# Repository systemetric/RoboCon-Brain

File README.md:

# RoboCon-Brain
Custom hardware and firmware for the RoboCon Brain, with PCB designs, embedded software and supporting files. Generations are documented through dedicated branches.

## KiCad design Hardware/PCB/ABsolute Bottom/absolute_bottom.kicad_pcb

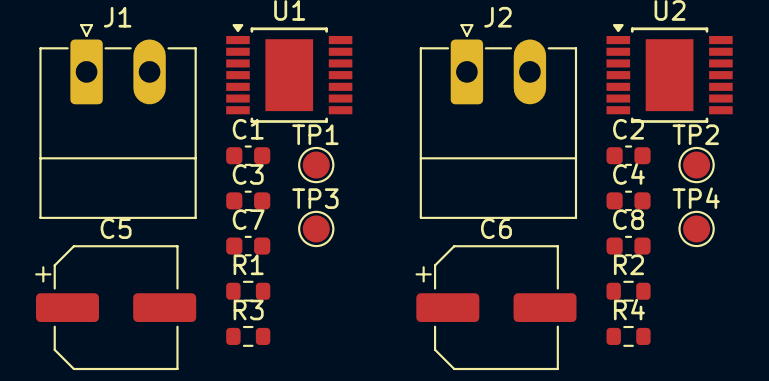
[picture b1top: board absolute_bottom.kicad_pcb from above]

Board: 2 copper layers, 20 parts (0 on the bottom side), 10 nets, no tracks yet.

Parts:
C1, C2, C3, C4: 0.1u; C_0603_1608Metric
C5, C6: 220u; CP_Elec_6.3x5.4_Nichicon
C7, C8: 10n; C_0603_1608Metric
J1, J2: M0; PhoenixContact_MC_1,5_2-G-3.5_1x02_P3.50mm_Horizontal
R1, R2, R3, R4: 1k; R_0603_1608Metric
TP1, TP2, TP3, TP4: TestPoint; TestPoint_Pad_D1.5mm
U1, U2: BTM9021EP; Infineon_PG-TSDSO-14-22

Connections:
+BATT: C1.1, C2.1, C3.1, C4.1, C5.1, C6.1, U1.11 (VS), U1.12 (VS), U2.11 (VS), U2.12 (VS)
/Motor 0/A: J1.1, TP1.1 (1_1), U1.1 (OUTA), U1.14 (OUTA)
/Motor 0/B: J1.2, TP3.1 (1_1), U1.7 (OUTB), U1.8 (OUTB)
/Motor 0/IS: C7.1, R3.1
/Motor 1/A: J2.1, TP2.1 (1_1), U2.1 (OUTA), U2.14 (OUTA)
/Motor 1/B: J2.2, TP4.1 (1_1), U2.7 (OUTB), U2.8 (OUTB)
/Motor 1/IS: C8.1, R4.1
GND: C1.2, C2.2, C3.2, C4.2, C5.2, C6.2, C7.2, C8.2, R1.2, R2.2, U1.3 (GND), U1.4 (GND), U1.5 (GND), U1.15 (GND), U2.3 (GND), U2.4 (GND), U2.5 (GND), U2.15 (GND)
unnamed: R1.1, R3.2, U1.13 (IS)
unnamed: R2.1, R4.2, U2.13 (IS)

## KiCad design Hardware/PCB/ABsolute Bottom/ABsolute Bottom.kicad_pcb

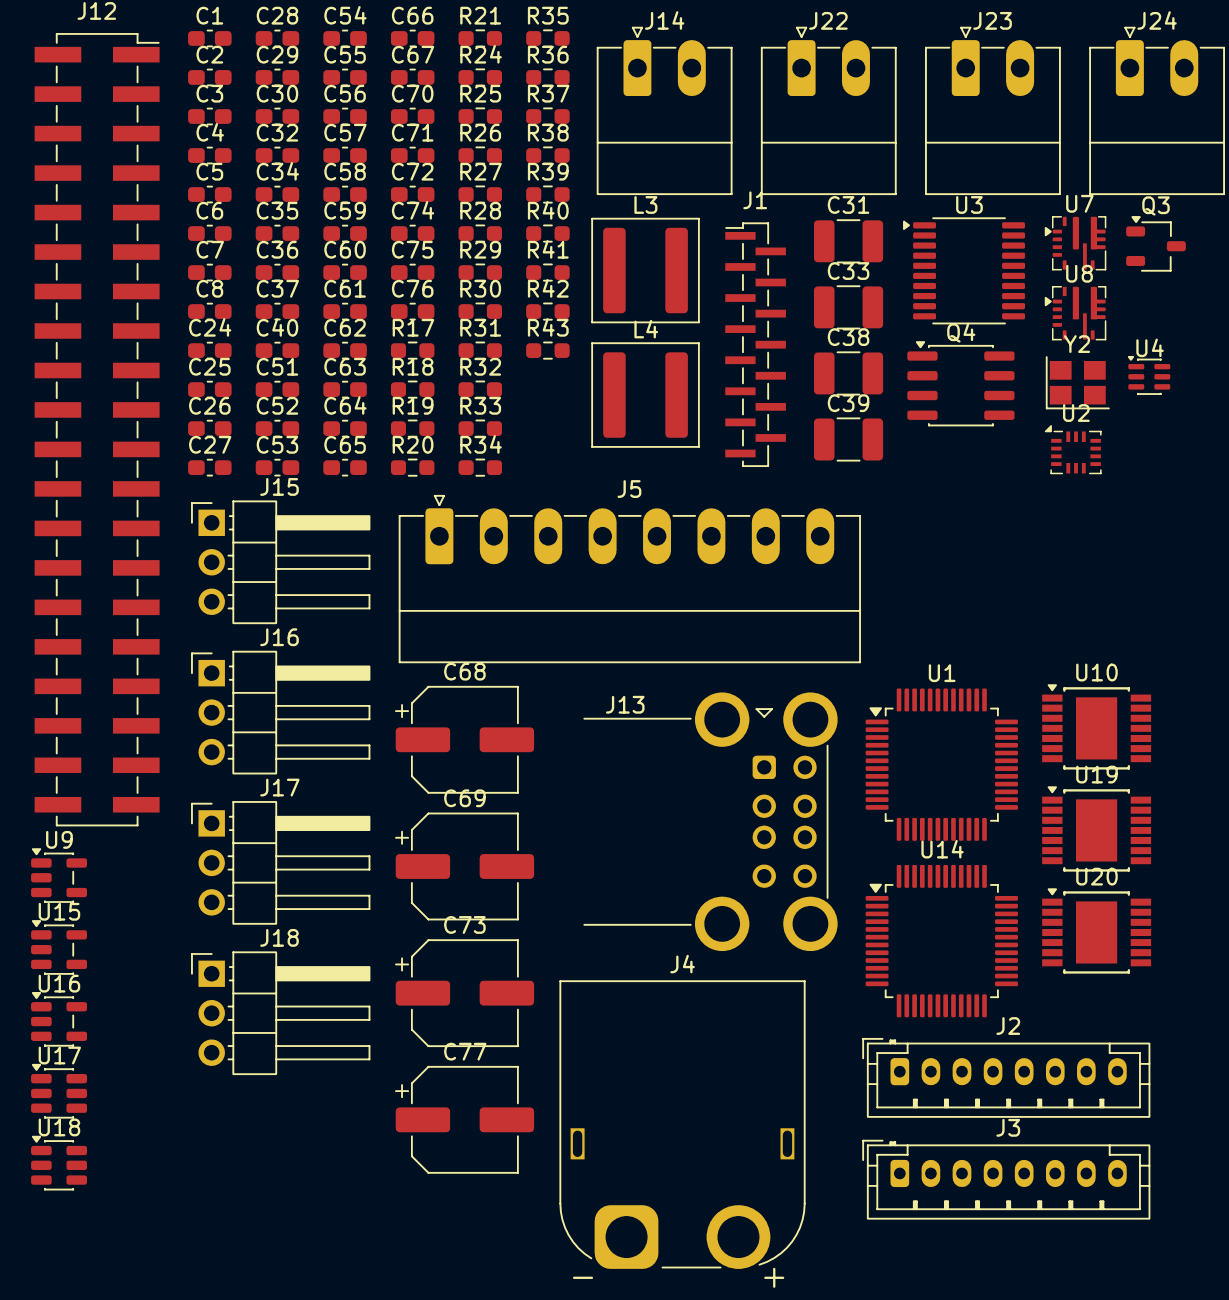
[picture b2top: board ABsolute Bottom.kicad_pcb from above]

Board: 4 copper layers, 112 parts (0 on the bottom side), 60 nets, no tracks yet.

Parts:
C1, C2, C4, C5, C7, C8, C26, C28, C34, C36, C40, C51, C53, C54, C56, C57, C58, C60, C61, C66, C67, C70, C71, C72, C74, C75, C76: 0.1u; C_0603_1608Metric_Pad1.08x0.95mm_HandSolder
C3, C6, C59, C62, C63, C64, C65: 4.7u; C_0603_1608Metric_Pad1.08x0.95mm_HandSolder
C24, C25, C30, C32: 10u; C_0603_1608Metric_Pad1.08x0.95mm_HandSolder
C27, C35: 47n; C_0603_1608Metric_Pad1.08x0.95mm_HandSolder
C29, C37: 150p; C_0603_1608Metric_Pad1.08x0.95mm_HandSolder
C31, C33, C38, C39: 22u; C_1210_3225Metric_Pad1.33x2.70mm_HandSolder
C52, C55: 20; C_0603_1608Metric_Pad1.08x0.95mm_HandSolder
C68, C69, C73, C77: 220u; CP_Elec_6.3x5.4_Nichicon
J1: Conn_01x15; PinSocket_1x15_P1.00mm_Vertical_SMD_Pin1Left
J2, J3: Conn_01x08; JST_PH_B8B-PH-K_1x08_P2.00mm_Vertical
J4: Conn_01x02; AMASS_XT60PW-M_1x02_P7.20mm_Horizontal
J5: Conn_01x08; PhoenixContact_MC_1,5_8-G-3.5_1x08_P3.50mm_Horizontal
J12: Conn_02x20; PinSocket_2x20_P2.54mm_Vertical_SMD
J13: AU-Y1008-2-BLK; USB_A_CUI_UJ2-ADH-TH_Horizontal_Stacked
J14, J22, J23, J24: Conn_01x02; PhoenixContact_MC_1,5_2-G-3.5_1x02_P3.50mm_Horizontal
J15, J16, J17, J18: Conn_01x03; PinHeader_1x03_P2.54mm_Horizontal
L3, L4: 3.3uH; L_Wuerth_XHMI-6060
Q3: BSS138; TSOT-23
Q4: SI4153DY-T1-GE3; SOIC-8_3.9x4.9mm_P1.27mm
R17, R24, R36, R37, R38: 100k; R_0603_1608Metric_Pad0.98x0.95mm_HandSolder
R18, R31: 52.3k; R_0603_1608Metric_Pad0.98x0.95mm_HandSolder
R19, R26, R27, R30, R32, R43: 10k; R_0603_1608Metric_Pad0.98x0.95mm_HandSolder
R20, R33: 49.9; R_0603_1608Metric_Pad0.98x0.95mm_HandSolder
R21: 22k; R_0603_1608Metric_Pad0.98x0.95mm_HandSolder
R25: 649; R_0603_1608Metric_Pad0.98x0.95mm_HandSolder
R28, R34: 73.2k; R_0603_1608Metric_Pad0.98x0.95mm_HandSolder
R29: 82k; R_0603_1608Metric_Pad0.98x0.95mm_HandSolder
R35, R42: 1k; R_0603_1608Metric_Pad0.98x0.95mm_HandSolder
R39: 47; R_0603_1608Metric_Pad0.98x0.95mm_HandSolder
R40, R41: 560; R_0603_1608Metric_Pad0.98x0.95mm_HandSolder
U1: AVR128DA48-I/PT; TQFP-48_7x7mm_P0.5mm
U2: BMI323; Bosch_LGA-14_3x2.5mm_P0.5mm
U3: TXS0108EPWR; TSSOP-20_4.4x6.5mm_P0.65mm
U4: SN74LVC1G3157; SOT-363_SC-70-6
U7, U8: TPS56A37RPAR; RPA0010A-MFG
U9, U15, U16: AP22804AW5-7; SOT-23-5
U10: BTS70021EPPXUMA1; Infineon_PG-TSDSO-14-22
U14: CY7C65632-48AXC; TQFP-48_7x7mm_P0.5mm
U17, U18: USBLC6-2SC6; SOT-23-6
U19, U20: BTM9021EP; Infineon_PG-TSDSO-14-22
Y2: ABM8-12MHz; Crystal_SMD_Abracon_ABM8AIG-4Pin_3.2x2.5mm

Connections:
+3.3V_PI: C4.1, C5.1, C6.1, C8.2, J12.2, J12.18, U2.5 (VDDIO), U2.8 (VDD), U3.2 (VCCA)
+3.3V_USB: C51.1, C53.1, C54.1, C56.1, C58.1, C60.1, C61.1, C62.1, C63.1, R26.1, R27.1, U14.1 (VCC_A), U14.7 (VCC_A_2), U14.12 (VCC_A_3), U14.16 (VCC_A_4), U14.19 (VCC_A_5), U14.25 (SEL48), U14.33 (SET_PORT_NUM2), U14.34 (VCC_D), U14.36 (PWR_PIN_POL), U14.37 (SELFPWR), U14.38 (VCC_D_2), U14.44 (SEL27), U14.48 (VREG)
+5V_AUX: C31.1, C33.1, J3.1, J3.2, J3.3, J3.4, J15.2, J16.2, J17.2, J18.2, J22.1, L3.2, R20.1
+5V_PI: C40.1, J12.1, J12.3, R38.1, U9.1 (OUT)
+5V_SYS: C1.1, C2.1, C3.1, C7.2, C38.1, C39.1, C57.1, C59.1, C64.1, C65.1, J1.1, J1.2, J1.3, J1.4, L4.2, R33.1, R37.2, U1.14 (VDD), U1.28 (AVDD), U1.42 (VDD), U3.19 (VCCB), U4.5 (VCC), U9.5 (IN), U14.47 (VCC), U15.5 (IN), U16.5 (IN)
+5V_USB1: C66.1, C68.1, J13.1 (VBUS1), U15.1 (OUT), U17.5 (VBUS)
+5V_USB2: C67.1, C69.1, J13.5 (VBUS2), U16.1 (OUT), U18.5 (VBUS)
+VBAT: J4.1, Q4.1 (S), Q4.2, Q4.3, R36.2, U10.15 (VS)
+VBAT_AUX: C71.1, C72.1, C73.1, C75.1, C76.1, C77.1, J2.1, J2.2, J2.3, J2.4, J14.1, U10.8 (OUT_1), U10.9 (OUT_2), U10.10 (OUT_3), U10.12 (OUT_4), U10.13 (OUT_5), U10.14 (OUT_6), U19.11 (VS), U19.12 (VS), U20.11 (VS), U20.12 (VS)
+VBAT_REG: C24.1, C25.1, C26.1, C30.1, C32.1, C34.1, Q4.5 (D), Q4.6, Q4.7, Q4.8, R21.1, R29.1, U7.8 (VIN), U8.8 (VIN)
/Controllers/LVL_OE: J12.11, U3.10 (OE)
/Controllers/MCU_UPDI: U3.15 (B5), U4.4
/Controllers/PI_RUNNING: J12.12, U3.4 (A3)
/Controllers/PI_SCL: J12.6, U3.3 (A2)
/Controllers/PI_SDA: J12.4, U3.1 (A1)
/Controllers/PI_SHUTDOWN: J12.14, U3.5 (A4)
/Controllers/PI_UPDI: J12.9, R42.2, U3.6 (A5)
/Controllers/UPDI_SEL: J12.15, U4.6
/Motors/M0_IS: C70.1, R40.2, U19.13 (IS)
/Motors/M0_OUT_A: J23.1, U19.1 (OUTA1), U19.14 (OUTA2)
/Motors/M0_OUT_B: J23.2, U19.7 (OUTB1), U19.8 (OUTB2)
/Motors/M1_IS: C74.1, R41.2, U20.13 (IS)
/Motors/M1_OUT_A: J24.1, U20.1 (OUTA1), U20.14 (OUTA2)
/Motors/M1_OUT_B: J24.2, U20.7 (OUTB1), U20.8 (OUTB2)
/Motors/MISO: U19.9 (SDO), U20.9 (SDO)
/Motors/MOSI: U19.2 (SDI), U20.2 (SDI)
/Motors/SCK: U19.6 (SCLK), U20.6 (SCLK)
/Power/5V_AUX_EN: R17.2, U7.1 (EN)
/Power/5V_PI_EN: R38.2, U9.4 (EN)
/Power/SW_POWER: Q3.3 (D), Q4.4 (G), R36.1
/Power/VBAT_SENSE: R21.2, R43.1
/USB/USB1_DN: J13.2 (D1-), U14.5 (DD-[1]), U17.3 (I/O2), U17.4 (I/O2)
/USB/USB1_DP: J13.3 (D1+), U14.6 (DD+[1]), U17.1 (I/O1), U17.6 (I/O1)
/USB/USB1_OVR: R26.2, U14.42 (OVR#[1]), U15.3 (~FLG)
/USB/USB1_PWR: U14.43 (PWR#[1]), U15.4 (EN)
/USB/USB2_DN: J13.6 (D2-), U14.9 (DD-[2]), U18.3 (I/O2), U18.4 (I/O2)
/USB/USB2_DP: J13.7 (D2+), U14.10 (DD+[2]), U18.1 (I/O1), U18.6 (I/O1)
/USB/USB2_OVR: R27.2, U14.40 (OVR#[2]), U16.3 (~FLG)
/USB/USB2_PWR: U14.41 (PWR#[2]), U16.4 (EN)
/USB/USB_XIN: C52.1, U14.14 (XIN), Y2.3
/USB/USB_XOUT: C55.2, U14.15 (XOUT), Y2.1
GND: C1.2, C2.2, C3.2, C4.2, C5.2, C6.2, C7.1, C8.1, C24.2, C25.2, C26.2, C27.2, C30.2, C31.2, C32.2, C33.2, C34.2, C35.2, C38.2, C39.2, C40.2, C51.2, C52.2, C53.2, C54.2, C55.1, C56.2, C57.2, C58.2, C59.2, C60.2, C61.2, C62.2, C63.2, C64.2, C65.2, C66.2, C67.2, C68.2, C69.2, C70.2, C71.2, C72.2, C73.2, C74.2, C75.2, C76.2, C77.2, J1.12, J1.13, J1.14, J1.15, J2.5, J2.6, J2.7, J2.8, J3.5, J3.6, J3.7, J3.8, J4.2, J12.5, J12.10, J12.13, J12.19, J12.26, J12.29, J12.33, J12.40, J13.4 (GND1), J13.8 (GND2), J14.2, J15.3, J16.3, J17.3, J18.3, J22.2, Q3.2 (S), R17.1, R18.2, R19.2, R24.2, R25.2, R30.2, R31.2, R32.2, R39.2, R40.1, R41.1, R43.2, U1.15 (GND), U1.29 (GND), U1.43 (GND), U2.6 (GNDIO), U2.7 (GND), U3.11 (GND), U4.2 (GND), U7.3 (AGND), U7.9 (PGND), U8.3 (AGND), U8.9 (PGND), U9.2 (GND), U14.2 (GND), U14.8 (GND_2), U14.13 (GND_3), U14.20 (GND_4), U14.24 (SET_PORT_NUM1), U14.27 (TEST), U15.2 (GND), U16.2 (GND), U17.2 (GND), U18.2 (GND), U19.3 (GND), U19.4 (GND), U19.5 (GND), U19.15 (EDP), U20.3 (GND), U20.4 (GND), U20.5 (GND), U20.15 (EDP), Y2.2 (G), Y2.4 (G)
unnamed: C29.1, R20.2, R28.1
unnamed: C37.1, R33.2, R34.1
unnamed: J12.7, R42.1
unnamed: Q3.1 (G), R35.2, R37.1
unnamed: C28.1, U7.7 (BOOT)
unnamed: C29.2, R19.1, R28.2, U7.2 (FB)
unnamed: R18.1, U7.10 (MODE)
unnamed: C27.1, U7.5 (SS)
unnamed: C28.2, L3.1, U7.6 (SW)
unnamed: C36.1, U8.7 (BOOT)
unnamed: R29.2, R30.1, U8.1 (EN)
unnamed: C37.2, R32.1, R34.2, U8.2 (FB)
unnamed: R31.1, U8.10 (MODE)
unnamed: C35.1, U8.5 (SS)
unnamed: C36.2, L4.1, U8.6 (SW)
unnamed: R39.1, U10.1 (GND)
unnamed: R24.1, U14.39 (GANG)
unnamed: R25.1, U14.11 (RREF)

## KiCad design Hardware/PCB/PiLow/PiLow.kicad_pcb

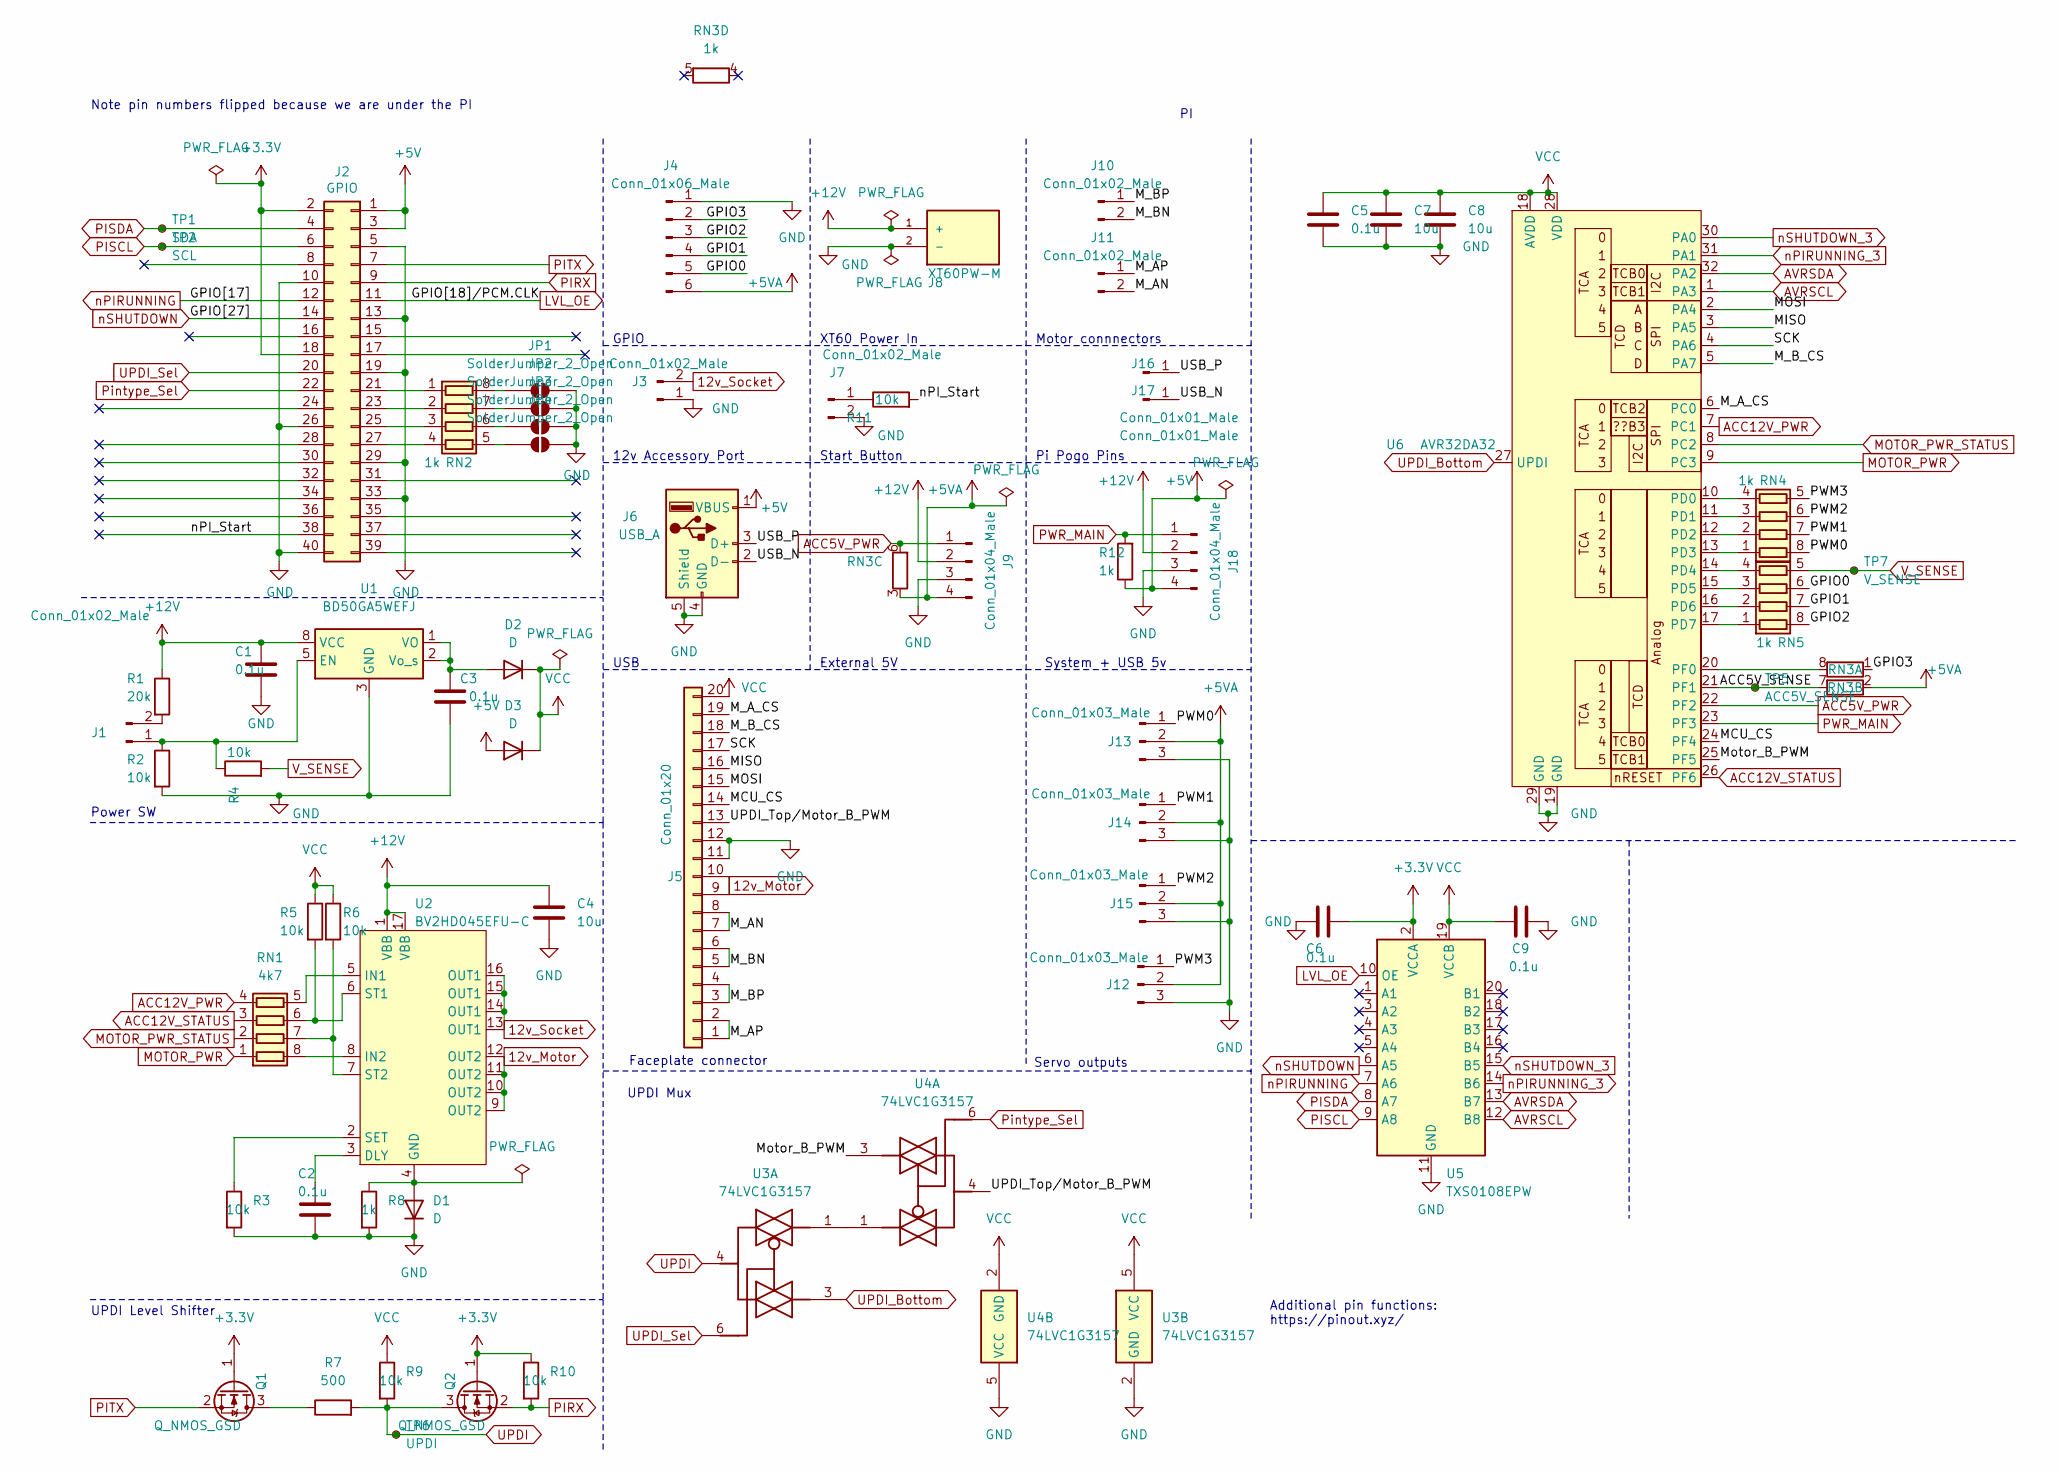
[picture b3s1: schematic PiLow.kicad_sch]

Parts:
C1, C2, C3, C5, C6, C9: 0.1u; C_0805_2012Metric_Pad1.18x1.45mm_HandSolder
C4, C7, C8: 10u; C_0805_2012Metric_Pad1.18x1.45mm_HandSolder
D1, D2, D3: D; D_SMA_Handsoldering
J1, J7: Conn_01x02_Male; PhoenixContact_MC_1,5_2-G-3.81_1x02_P3.81mm_Horizontal
J2: GPIO; PinSocket_2x20_P2.54mm_Vertical_SMD
J3, J10, J11: Conn_01x02_Male; PhoenixContact_MC_1,5_2-G-5.08_1x02_P5.08mm_Horizontal
J4: Conn_01x06_Male; PhoenixContact_MC_1,5_6-G-3.81_1x06_P3.81mm_Horizontal
J5: Conn_01x20; PinHeader_1x20_P2.54mm_Vertical
J6: USB_A; USB_A_Wuerth_614004134726_Horizontal
J8: XT60PW-M; AMASS_XT60PW-M; PARTREV V1.2
J9, J18: Conn_01x04_Male; PinHeader_1x04_P2.54mm_Vertical
J12, J13, J14, J15: Conn_01x03_Male; PinHeader_1x03_P2.54mm_Horizontal
J16, J17: Conn_01x01_Male; PinHeader_1x01_P2.54mm_Vertical
JP1, JP2, JP3, JP4: SolderJumper_2_Open; SolderJumper-2_P1.3mm_Open_TrianglePad1.0x1.5mm
Q1, Q2: Q_NMOS_GSD; SOT-23_Handsoldering
R1: 20k; R_0805_2012Metric_Pad1.20x1.40mm_HandSolder
R2, R3, R4, R5, R6, R9, R10, R11: 10k; R_0805_2012Metric_Pad1.20x1.40mm_HandSolder
R7: 500; R_0805_2012Metric_Pad1.20x1.40mm_HandSolder
R8, R12: 1k; R_0805_2012Metric_Pad1.20x1.40mm_HandSolder
RN1: 4k7; R_Array_Convex_4x0612
RN2, RN3, RN4, RN5: 1k; R_Array_Convex_4x0612
TP1: SDA; TestPoint_Pad_D1.5mm
TP2: SCL; TestPoint_Pad_D1.5mm
TP5: ACC5V_SENSE; TestPoint_Pad_D1.5mm
TP6: UPDI; TestPoint_Pad_D1.5mm
TP7: V_SENSE; TestPoint_Pad_D1.5mm
U1: BD50GA5WEFJ; HTSOP-8-1EP_3.9x4.9mm_P1.27mm_EP2.4x3.2mm
U2: BV2HD045EFU-C; HSSOP-C16
U3, U4: 74LVC1G3157; SOT-363_SC-70-6
U5: TXS0108EPW; TSSOP-20_4.4x6.5mm_P0.65mm
U6: AVR32DA32; TQFP-32_7x7mm_P0.8mm

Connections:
12v_Motor: J5.9, J5.10, U2.9 (OUT2), U2.10 (OUT2), U2.11 (OUT2), U2.12 (OUT2)
12v_Socket: J3.2, U2.13 (OUT1), U2.14 (OUT1), U2.15 (OUT1), U2.16 (OUT1)
+3.3V: C6.1, J2.2, J2.18, Q1.1 (G), Q2.1 (G), R10.1, U5.2 (VCCA)
+5V: D3.2 (A), J2.1, J2.3, J6.1 (VBUS), J18.4, R12.1
+5VA: J4.6, J9.4, J12.2, J13.2, J14.2, J15.2, RN3.2 (R2.1), RN3.3 (R3.1)
+12V: C1.1, C4.1, J8.1 (+), J9.2, J18.2, R1.1, U1.8 (VCC), U2.1 (VBB), U2.17 (VBB)
/ACC5V_SENSE: RN3.7 (R2.2), TP5.1 (1_1), U6.21 (PF1)
/GPIO0: J4.5, RN5.6 (R3.2)
/GPIO1: J4.4, RN5.7 (R2.2)
/GPIO2: J4.3, RN5.8 (R1.2)
/GPIO3: J4.2, RN3.1 (R1.1)
/MCU_CS: J5.14, U6.24 (PF4)
/MISO: J5.16, U6.3 (PA5)
/MOSI: J5.15, U6.2 (PA4)
/M_AN: J5.7, J5.8, J11.2
/M_AP: J5.1, J5.2, J11.1
/M_A_CS: J5.19, U6.6 (PC0)
/M_BN: J5.5, J5.6, J10.2
/M_BP: J5.3, J5.4, J10.1
/M_B_CS: J5.18, U6.5 (PA7)
/Motor_B_PWM: U4.3, U6.25 (PF5)
/PWM0: J13.1, RN4.8 (R1.2)
/PWM1: J14.1, RN4.7 (R2.2)
/PWM2: J15.1, RN4.6 (R3.2)
/PWM3: J12.1, RN4.5 (R4.2)
/SCK: J5.17, U6.4 (PA6)
/UPDI_Top/Motor_B_PWM: J5.13, U4.4
/USB_N: J6.2 (D-), J17.1 (Pin_1_1)
/USB_P: J6.3 (D+), J16.1 (Pin_1_1)
/nPI_Start: J2.38, R11.2
ACC5V_PWR: J9.1, RN3.6 (R3.2), U6.22 (PF2)
ACC12V_PWR: RN1.4 (R4.1), U6.7 (PC1)
ACC12V_STATUS: RN1.3 (R3.1), U6.26 (PF6)
AVRSCL: U5.12 (B8), U6.1 (PA3)
AVRSDA: U5.13 (B7), U6.32 (PA2)
GND: C1.2, C2.2, C3.2, C4.2, C5.2, C6.2, C7.2, C8.2, C9.2, D1.1 (K), J2.5, J2.10, J2.13, J2.19, J2.26, J2.29, J2.33, J2.40, J3.1, J4.1, J5.11, J5.12, J6.4 (GND), J6.5 (Shield), J7.2, J8.2 (-), J9.3, J12.3, J13.3, J14.3, J15.3, J18.3, JP1.2 (B), JP2.2 (B), JP3.2 (B), JP4.2 (B), R2.2, R3.2, R8.2, U1.3 (GND), U1.4 (GND), U1.6 (GND), U1.7 (GND), U1.9 (GND), U3.2 (GND), U4.5 (VCC), U5.11 (GND), U6.19 (GND), U6.29 (GND)
LVL_OE: J2.11, U5.10 (OE)
MOTOR_PWR: RN1.1 (R1.1), U6.9 (PC3)
MOTOR_PWR_STATUS: RN1.2 (R2.1), U6.8 (PC2)
unnamed: D1.2 (A), R8.1, U2.4 (GND)
unnamed: C3.1, D2.2 (A), U1.1 (VO), U1.2 (Vo_s)
unnamed: J1.1, R2.1, R4.1, U1.5 (EN)
unnamed: J1.2, R1.2
unnamed: J2.21, RN2.1 (R1.1)
unnamed: J2.23, RN2.2 (R2.1)
unnamed: J2.25, RN2.3 (R3.1)
unnamed: J2.27, RN2.4 (R4.1)
unnamed: J7.1, R11.1
unnamed: JP1.1 (A), RN2.8 (R1.2)
unnamed: JP2.1 (A), RN2.7 (R2.2)
unnamed: JP3.1 (A), RN2.6 (R3.2)
unnamed: JP4.1 (A), RN2.5 (R4.2)
unnamed: Q1.3 (D), R7.1
unnamed: RN1.8 (R1.2), U2.8 (IN2)
unnamed: R6.2, RN1.7 (R2.2), U2.7 (ST2)
unnamed: R5.2, RN1.6 (R3.2), U2.6 (ST1)
unnamed: RN1.5 (R4.2), U2.5 (IN1)
unnamed: RN3.8 (R1.2), U6.20 (PF0)
unnamed: RN4.1 (R1.1), U6.13 (PD3)
unnamed: RN4.2 (R2.1), U6.12 (PD2)
unnamed: RN4.3 (R3.1), U6.11 (PD1)
unnamed: RN4.4 (R4.1), U6.10 (PD0)
unnamed: RN5.1 (R1.1), U6.17 (PD7)
unnamed: RN5.2 (R2.1), U6.16 (PD6)
unnamed: RN5.3 (R3.1), U6.15 (PD5)
unnamed: RN5.4 (R4.1), U6.14 (PD4)
unnamed: C2.1, U2.3 (DLY)
unnamed: R3.1, U2.2 (SET)
unnamed: U3.1, U4.1
PIRX: J2.9, Q2.2 (S), R10.2
PISCL: J2.6, TP2.1 (1_1), U5.9 (A8)
PISDA: J2.4, TP1.1 (1_1), U5.8 (A7)
PITX: J2.7, Q1.2 (S)
PWR_MAIN: J18.1, R12.2, U6.23 (PF3)
Pintype_Sel: J2.22, U4.6
UPDI: Q2.3 (D), R7.2, R9.2, TP6.1 (1_1), U3.4
UPDI_Bottom: U3.3, U6.27 (UPDI)
UPDI_Sel: J2.20, U3.6
VCC: C5.1, C7.1, C8.1, C9.1, D2.1 (K), D3.1 (K), J5.20, R5.1, R6.1, R9.1, U3.5 (VCC), U4.2 (GND), U5.19 (VCCB), U6.18 (AVDD), U6.28 (VDD)
V_SENSE: R4.2, RN5.5 (R4.2), TP7.1 (1_1)
nPIRUNNING: J2.12, U5.7 (A6)
nPIRUNNING_3: U5.14 (B6), U6.31 (PA1)
nSHUTDOWN: J2.14, U5.6 (A5)
nSHUTDOWN_3: U5.15 (B5), U6.30 (PA0)

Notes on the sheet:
USB
External 5V
Faceplate connector
Additional pin functions: https://pinout.xyz/
Pi Pogo Pins
12v Accessory Port
UPDI Level Shifter
System + USB 5v
Servo outputs
Power SW
XT60 Power In
Start Button
UPDI Mux
GPIO
Note pin numbers flipped because we are under the PI
Motor connnectors

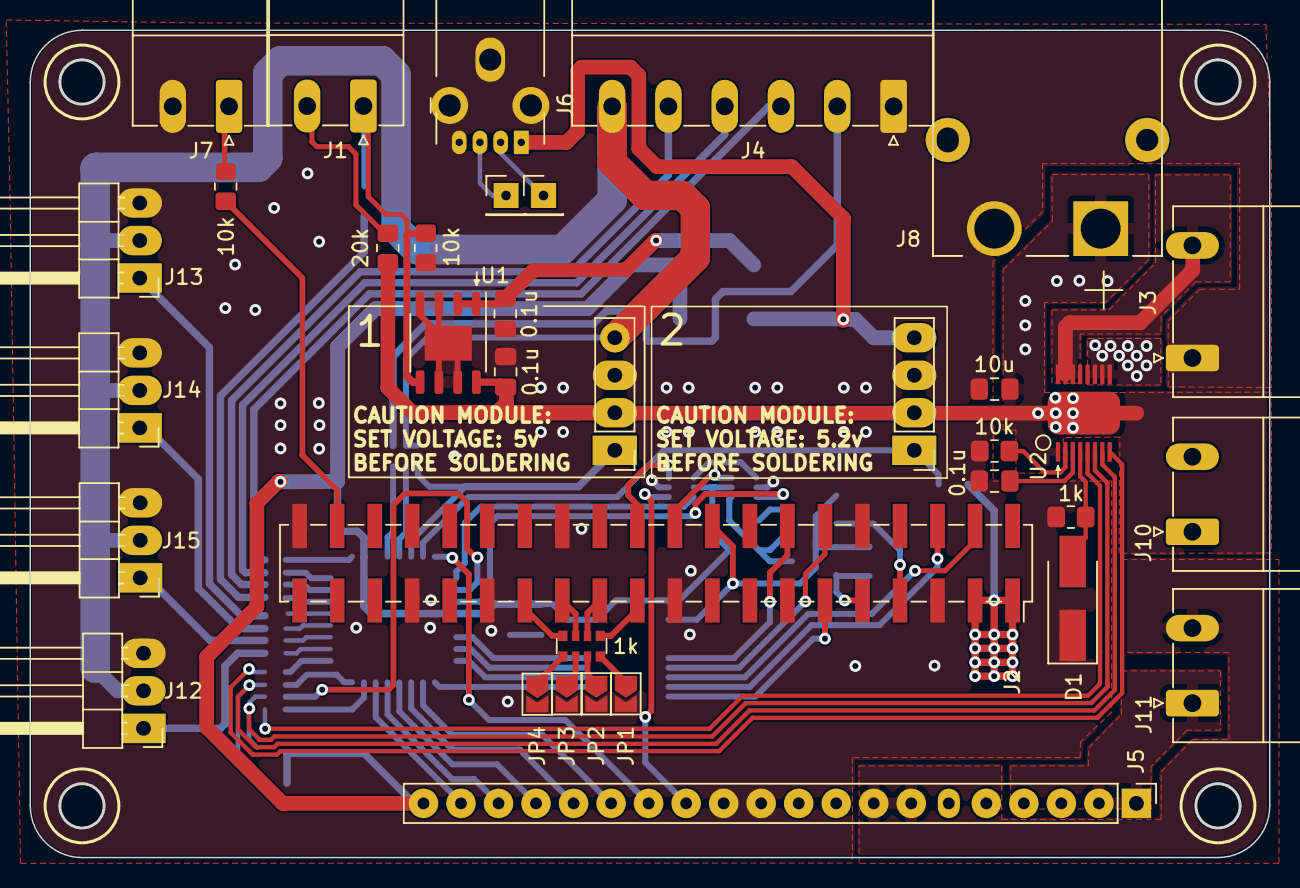
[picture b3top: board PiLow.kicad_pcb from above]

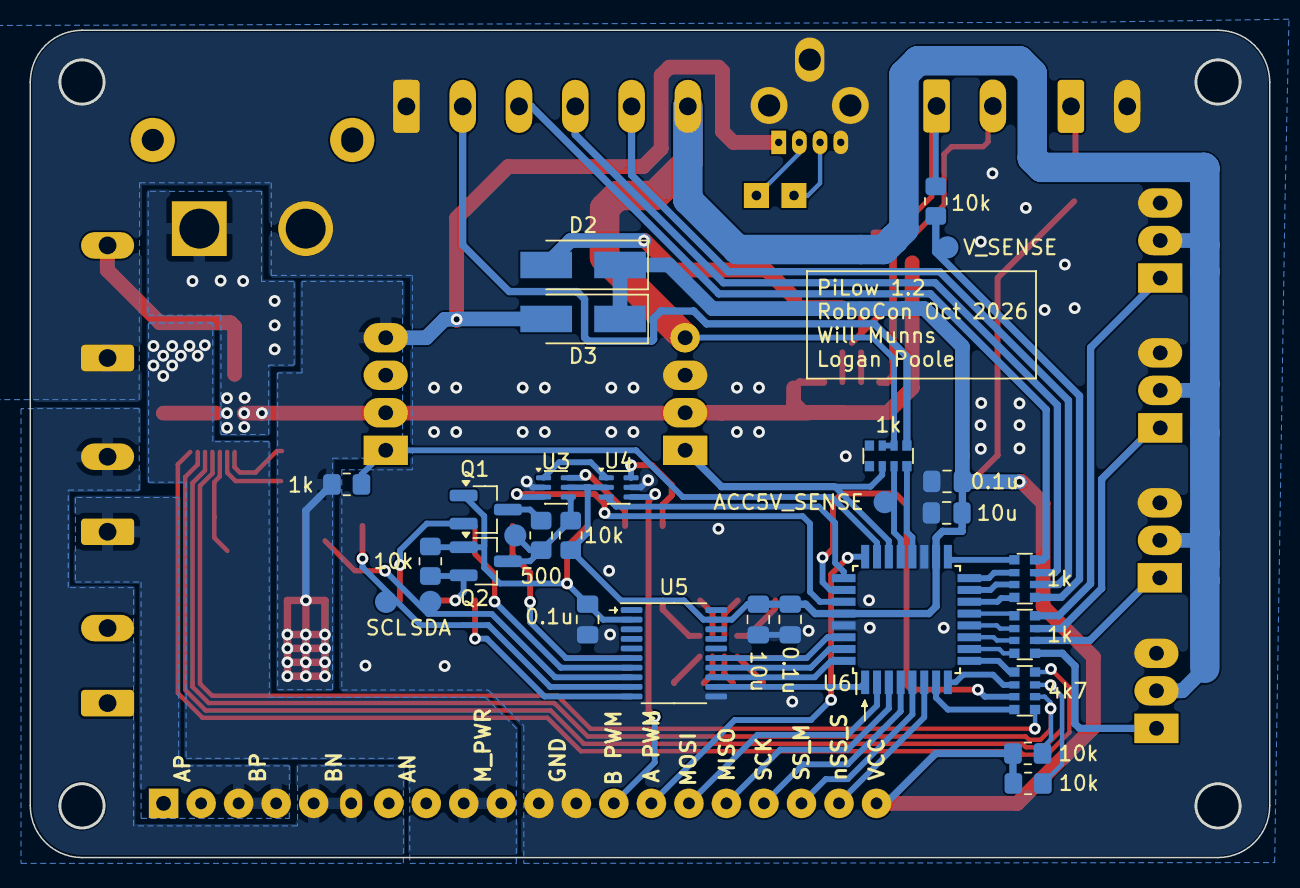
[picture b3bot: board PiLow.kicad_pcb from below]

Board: 2 copper layers, 83.9 x 56.0 mm, 64 parts (29 on the bottom side), 84 nets.

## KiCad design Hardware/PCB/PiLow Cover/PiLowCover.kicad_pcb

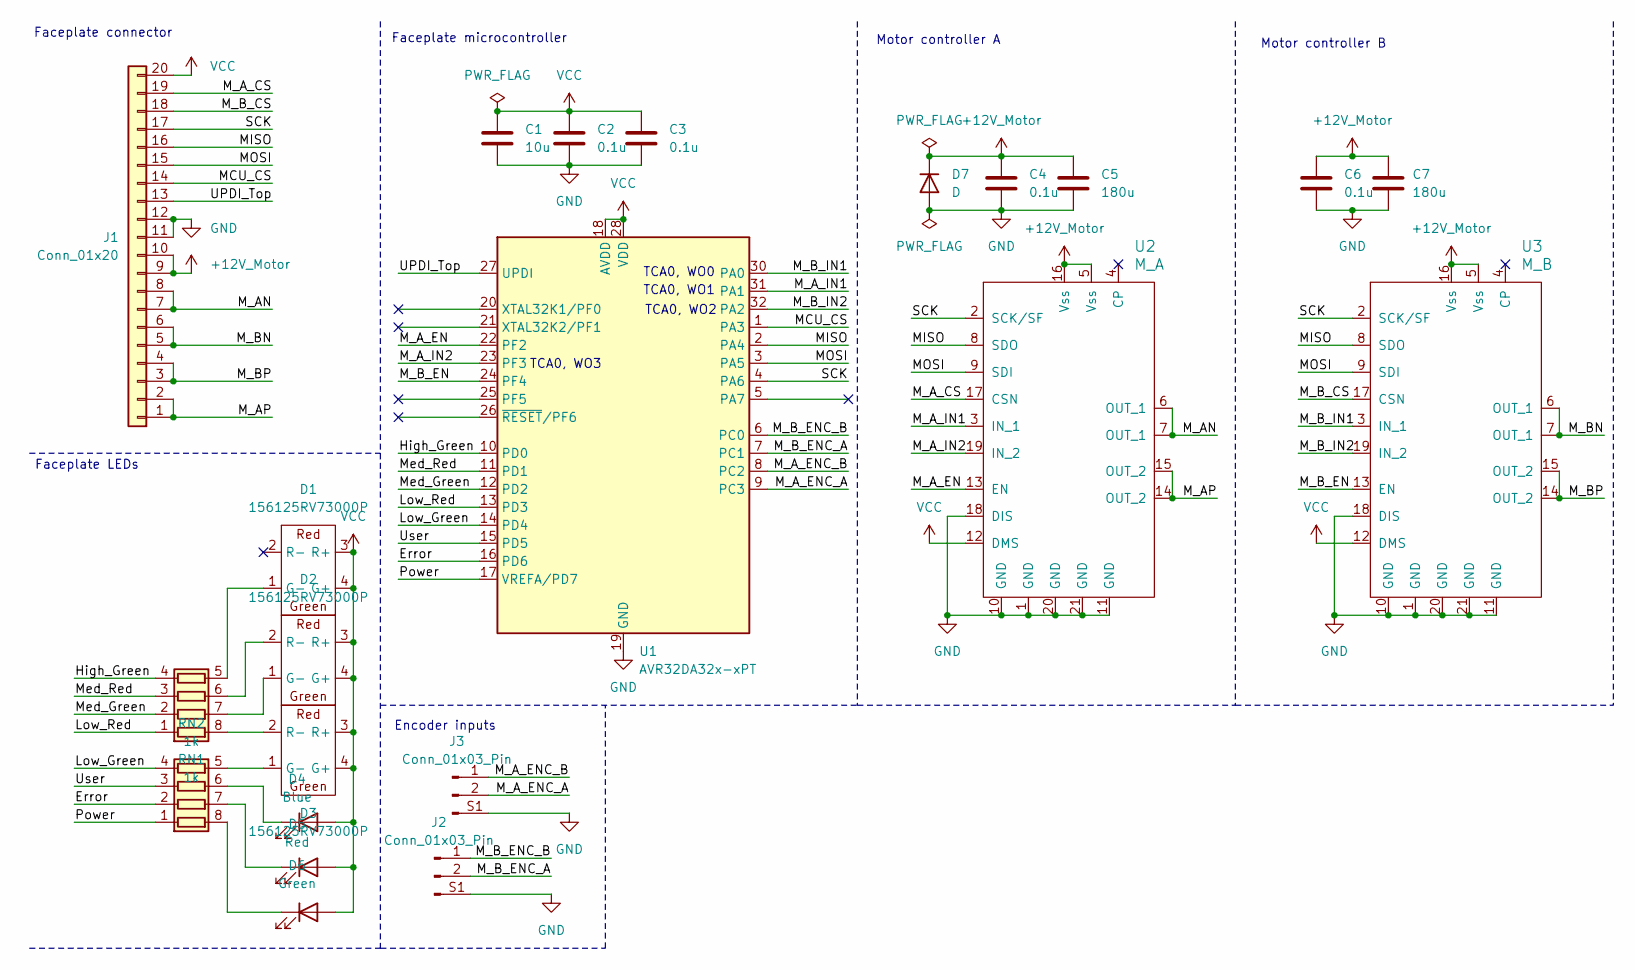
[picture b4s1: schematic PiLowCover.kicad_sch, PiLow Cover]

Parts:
C1: 10u; C_0805_2012Metric_Pad1.18x1.45mm_HandSolder
C2, C3, C4, C6: 0.1u; C_0805_2012Metric_Pad1.18x1.45mm_HandSolder
C5, C7: 180u; CP_Elec_6.3x5.4
D1, D2, D3: 156125RV73000P; WL-SBRW
D4: Blue; WL-SMRW
D5: Red; WL-SMRW
D6: Green; WL-SMRW
D7: D; D_SMA_Handsoldering
J1: Conn_01x20; PinHeader_1x20_P2.54mm_Vertical_SMD_Pin1Left
J2, J3: Conn_01x03_Pin; JST_S2B-PH-SM4-TB_LF__SN_
RN1, RN2: 1k; R_Array_Convex_4x0612
U1: AVR32DA32x-xPT; TQFP-32_7x7mm_P0.8mm
U2: M_A; HSOP-20-1EP_11.0x15.9mm_P1.27mm_SlugDown_ThermalVias
U3: M_B; HSOP-20-1EP_11.0x15.9mm_P1.27mm_SlugDown_ThermalVias

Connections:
+12V_Motor: C4.1, C5.1, C6.1, C7.1, D7.1 (K), J1.9, J1.10, U2.5 (Vss), U2.16 (Vss), U3.5 (Vss), U3.16 (Vss)
/Error: RN2.2 (R2.1), U1.16 (PD6)
/High_Green: RN1.4 (R4.1), U1.10 (PD0)
/Low_Green: RN2.4 (R4.1), U1.14 (PD4)
/Low_Red: RN1.1 (R1.1), U1.13 (PD3)
/MCU_CS: J1.14, U1.1 (PA3)
/MISO: J1.16, U1.2 (PA4), U2.8 (SDO), U3.8 (SDO)
/MOSI: J1.15, U1.3 (PA5), U2.9 (SDI), U3.9 (SDI)
/M_AN: J1.7, J1.8, U2.6 (OUT_1), U2.7 (OUT_1)
/M_AP: J1.1, J1.2, U2.14 (OUT_2), U2.15 (OUT_2)
/M_A_CS: J1.19, U2.17 (CSN)
/M_A_EN: U1.22 (PF2), U2.13 (EN)
/M_A_ENC_A: J3.2, U1.9 (PC3)
/M_A_ENC_B: J3.1, U1.8 (PC2)
/M_A_IN1: U1.31 (PA1), U2.3 (IN_1)
/M_A_IN2: U1.23 (PF3), U2.19 (IN_2)
/M_BN: J1.5, J1.6, U3.6 (OUT_1), U3.7 (OUT_1)
/M_BP: J1.3, J1.4, U3.14 (OUT_2), U3.15 (OUT_2)
/M_B_CS: J1.18, U3.17 (CSN)
/M_B_EN: U1.24 (PF4), U3.13 (EN)
/M_B_ENC_A: J2.2, U1.7 (PC1)
/M_B_ENC_B: J2.1, U1.6 (PC0)
/M_B_IN1: U1.30 (PA0), U3.3 (IN_1)
/M_B_IN2: U1.32 (PA2), U3.19 (IN_2)
/Med_Green: RN1.2 (R2.1), U1.12 (PD2)
/Med_Red: RN1.3 (R3.1), U1.11 (PD1)
/Power: RN2.1 (R1.1), U1.17 (VREFA/PD7)
/SCK: J1.17, U1.4 (PA6), U2.2 (SCK/SF), U3.2 (SCK/SF)
/UPDI_Top: J1.13, U1.27 (UPDI)
/User: RN2.3 (R3.1), U1.15 (PD5)
GND: C1.2, C2.2, C3.2, C4.2, C5.2, C6.2, C7.2, D7.2 (A), J1.11, J1.12, J2.S1 (Pin_3), J2.S2 (Pin_4), J3.S1 (Pin_3), J3.S2 (Pin_4), U1.19 (GND), U1.29 (GND), U2.1 (GND), U2.10 (GND), U2.11 (GND), U2.18 (DIS), U2.20 (GND), U2.21 (GND), U3.1 (GND), U3.10 (GND), U3.11 (GND), U3.18 (DIS), U3.20 (GND), U3.21 (GND)
unnamed: D1.1 (G-), RN1.5 (R4.2)
unnamed: D2.1 (G-), RN1.7 (R2.2)
unnamed: D2.2 (R-), RN1.6 (R3.2)
unnamed: D3.1 (G-), RN2.5 (R4.2)
unnamed: D3.2 (R-), RN1.8 (R1.2)
unnamed: D4.1 (K), RN2.6 (R3.2)
unnamed: D5.1 (K), RN2.7 (R2.2)
unnamed: D6.1 (K), RN2.8 (R1.2)
VCC: C1.1, C2.1, C3.1, D1.3 (R+), D1.4 (G+), D2.3 (R+), D2.4 (G+), D3.3 (R+), D3.4 (G+), D4.2 (A), D5.2 (A), D6.2 (A), J1.20, U1.18 (AVDD), U1.28 (VDD), U2.12 (DMS), U3.12 (DMS)

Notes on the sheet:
TCA0, WO2
TCA0, WO0
Encoder inputs
Faceplate LEDs
Motor controller A
TCA0, WO3
Motor controller B
Faceplate microcontroller
Faceplate connector
TCA0, WO1

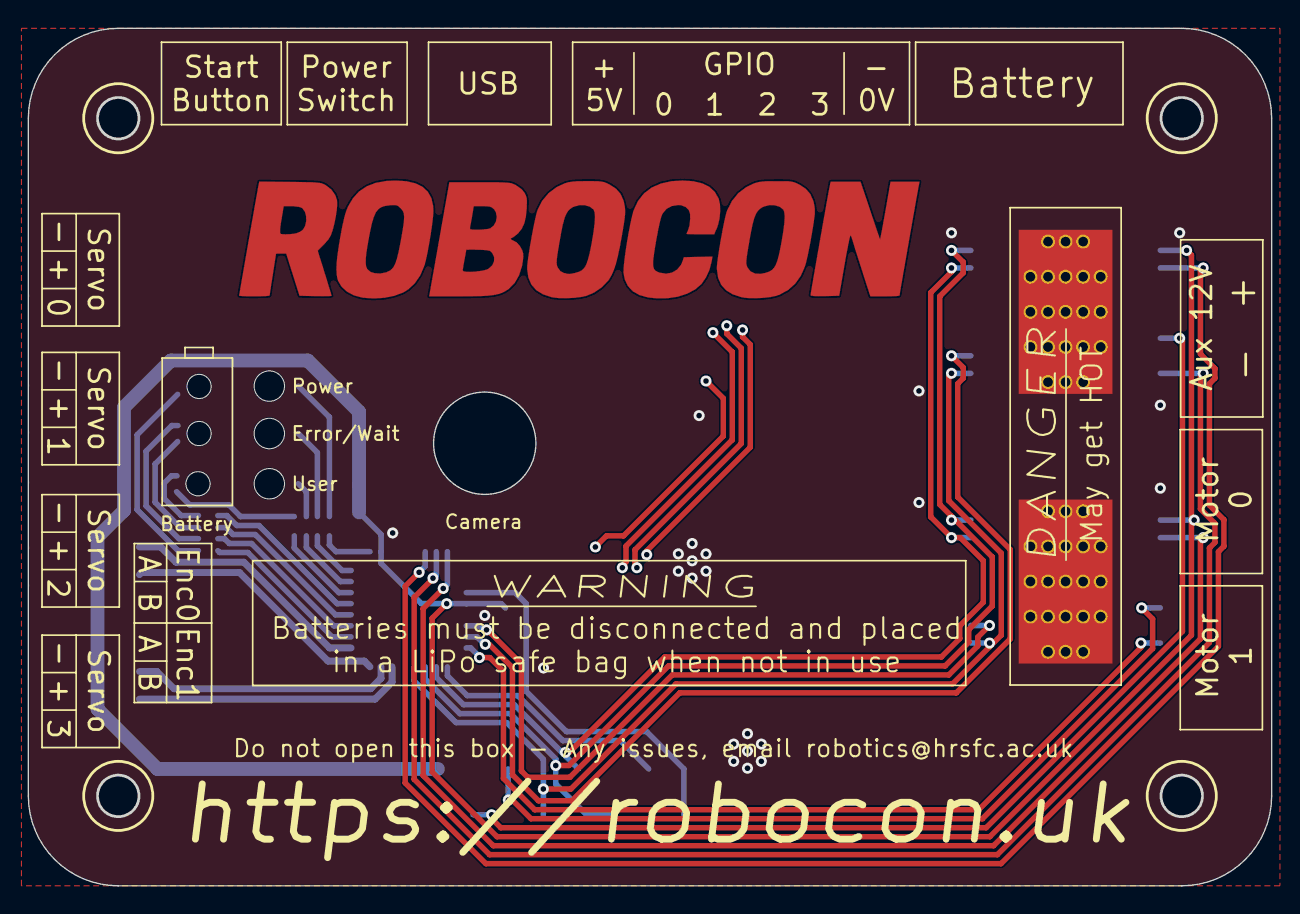
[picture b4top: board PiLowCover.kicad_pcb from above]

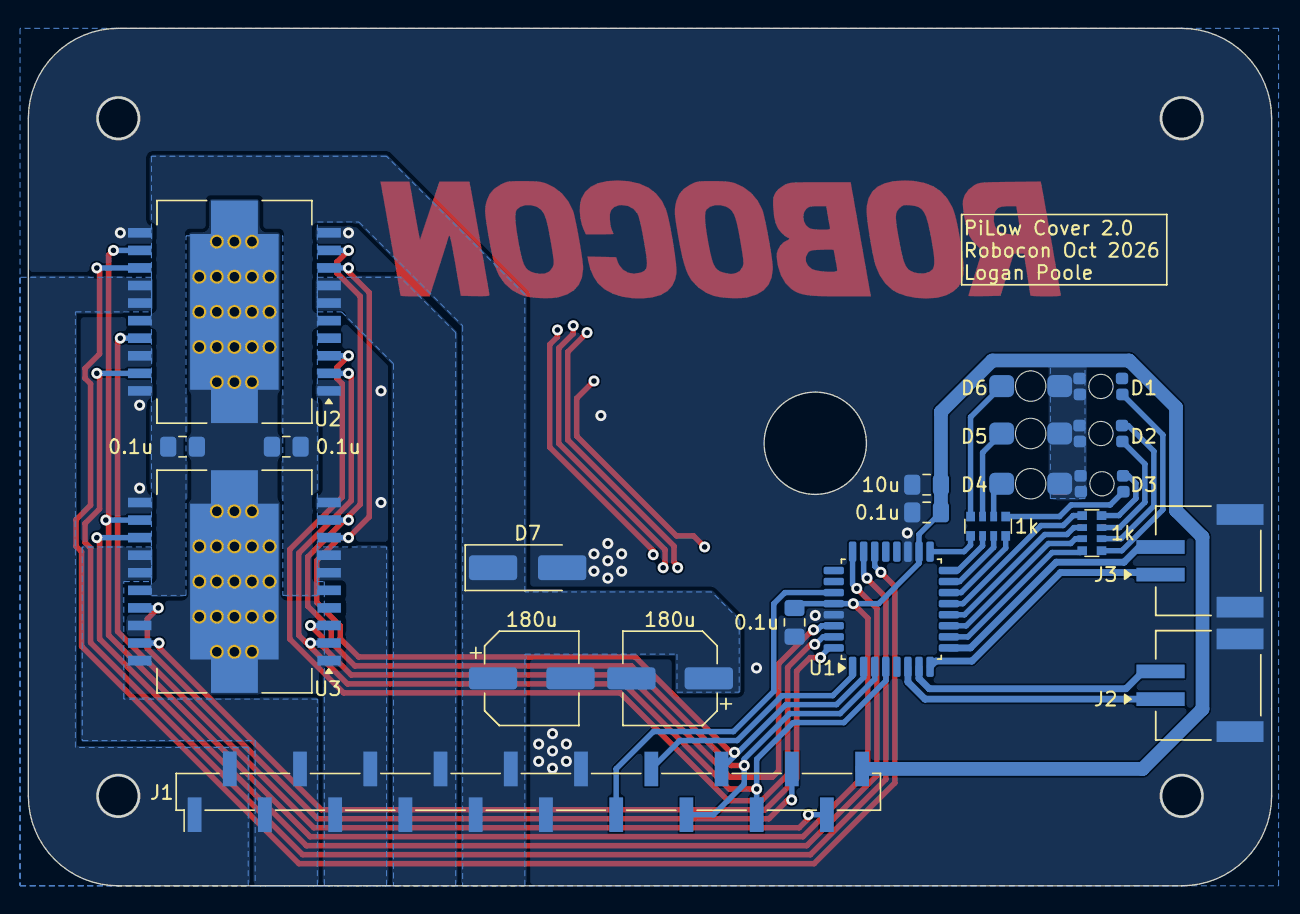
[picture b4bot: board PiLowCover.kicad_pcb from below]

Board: 2 copper layers, 89.9 x 62.0 mm, 22 parts (22 on the bottom side), 40 nets.
